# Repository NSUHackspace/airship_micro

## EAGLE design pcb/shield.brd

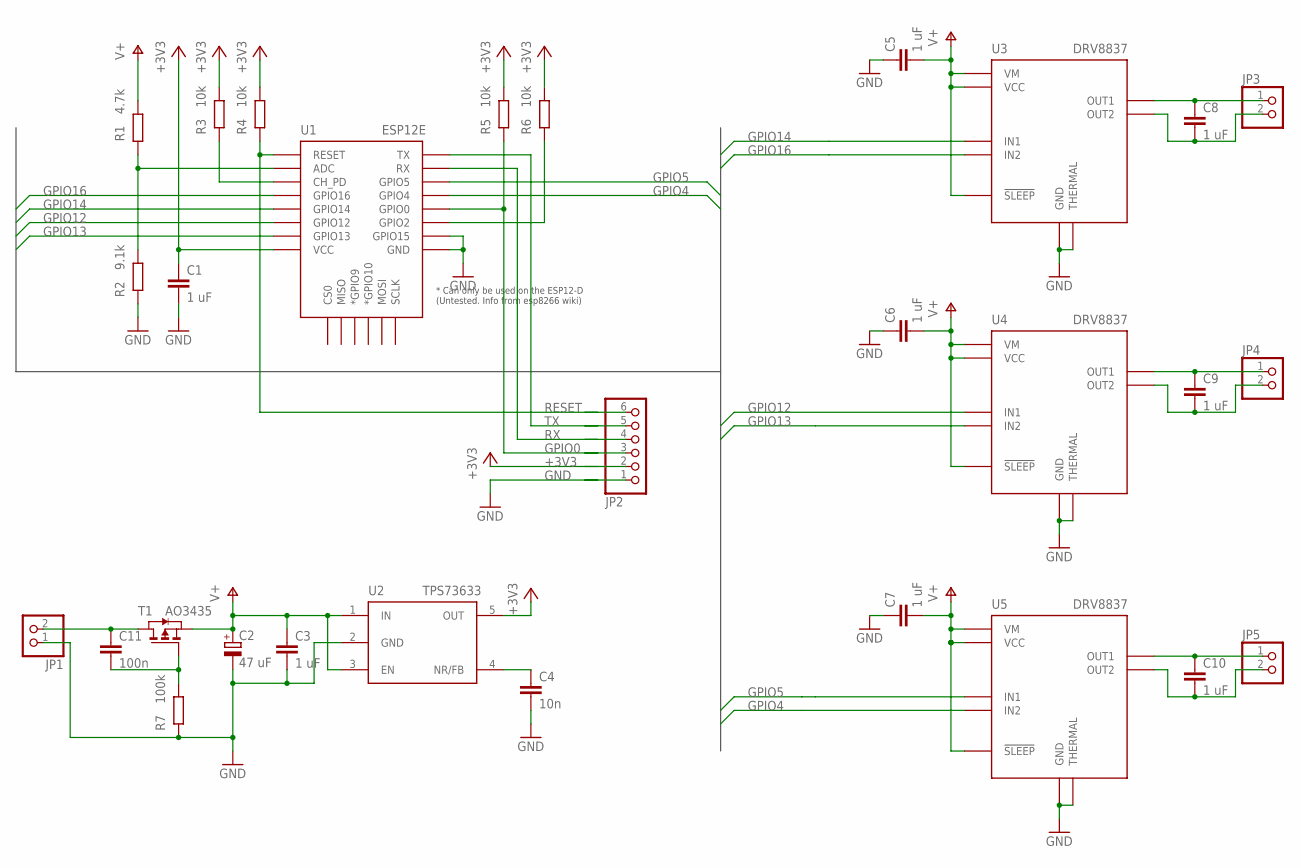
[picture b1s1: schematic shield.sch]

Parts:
C1, C3, C5, C6, C7, C8, C9, C10: 1 uF; C0805
C2: 47 uF; SMC_A
C4: 10n; C0603
C11: 100n; C0603
JP1, JP3, JP4, JP5: PINHD-1X2; 1X02
JP2: PINHD-1X6; 1X06
R1: 4.7k; R0603
R2: 9.1k; R0603
R3, R4, R5, R6: 10k; R0603
R7: 100k; R0603
T1: AO3435; SOT-23
U1: ESP12E; ESP12E-SMD
U2: TPS73633; SOT23-5L
U3, U4, U5: DRV8837; QFN8

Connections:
+3V3: C1.1, JP2.2, R3.2, R4.2, R5.2, R6.2, U1.VCC, U2.5 (OUT)
GND: C1.2, C2.-, C3.2, C4.2, C5.1, C6.1, C7.1, JP1.1, JP2.1, R2.1, R7.1, U1.GND, U1.GPIO15, U2.2 (GND), U3.P$4 (GND), U3.P$9 (THERMAL), U4.P$4 (GND), U4.P$9 (THERMAL), U5.P$4 (GND), U5.P$9 (THERMAL)
GPIO0: JP2.3, R5.1, U1.GPIO0
GPIO4: U1.GPIO4, U5.P$5 (IN2)
GPIO5: U1.GPIO5, U5.P$6 (IN1)
GPIO12: U1.GPIO12, U4.P$6 (IN1)
GPIO13: U1.GPIO13, U4.P$5 (IN2)
GPIO14: U1.GPIO14, U3.P$6 (IN1)
GPIO16: U1.GPIO16, U3.P$5 (IN2)
unnamed: R3.1, U1.CH_PD
unnamed: R6.1, U1.GPIO2
unnamed: C8.1, JP3.1, U3.P$2 (OUT1)
unnamed: C8.2, JP3.2, U3.P$3 (OUT2)
unnamed: C9.1, JP4.1, U4.P$2 (OUT1)
unnamed: C9.2, JP4.2, U4.P$3 (OUT2)
unnamed: C10.1, JP5.1, U5.P$2 (OUT1)
unnamed: C10.2, JP5.2, U5.P$3 (OUT2)
unnamed: R1.1, R2.2, U1.ADC
unnamed: C4.1, U2.4 (NR/FB)
unnamed: C11.1, JP1.2, T1.1 (D)
unnamed: C11.2, R7.2, T1.3 (G)
RESET: JP2.6, R4.1, U1.RESET
RX: JP2.4, U1.RXD0 (RX)
TX: JP2.5, U1.TXD0 (TX)
V+: C2.+, C3.1, C5.2, C6.2, C7.2, R1.2, T1.2 (S), U2.1 (IN), U2.3 (EN), U3.P$1 (VM), U3.P$7 (!SLEEP), U3.P$8 (VCC), U4.P$1 (VM), U4.P$7 (!SLEEP), U4.P$8 (VCC), U5.P$1 (VM), U5.P$7 (!SLEEP), U5.P$8 (VCC)

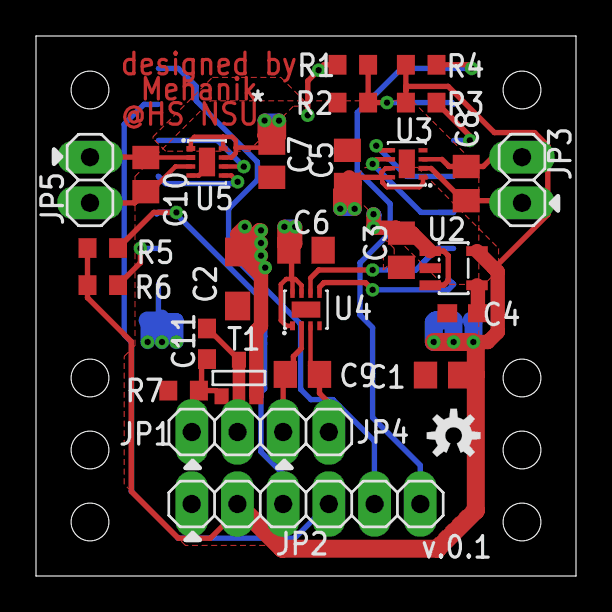
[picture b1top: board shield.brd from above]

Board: 2 copper layers, 30.0 x 30.0 mm, 29 parts (1 on the bottom side), 25 nets.

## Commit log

2019-03-09 Update stl models
